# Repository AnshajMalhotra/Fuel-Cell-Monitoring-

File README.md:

# Project Seminar SS2025 — Fuel Cell Monitoring Board

A mixed-signal hardware and firmware project for monitoring fuel-cell voltage and current using a custom KiCad PCB, precision analog front-end, isolated SPI data path, 16-bit ADC acquisition, and ESP32-S3 based data processing.

This repository combines the complete PCB design files and embedded firmware developed for the **Project Seminar SS2025**. The board is intended to acquire fuel-cell electrical measurements, convert raw ADC data into physical voltage/current values, and stream the processed measurements to a host system over serial communication.

---

## Repository Description

**Short GitHub description:**

> KiCad + ESP32-S3 fuel-cell monitoring board with precision voltage/current sensing, 16-bit SPI ADC acquisition, digital isolation, and PlatformIO firmware for averaged serial data output.

---

## Project Overview

The project focuses on designing and implementing a fuel-cell monitoring board that can measure:

- Fuel-cell voltage
- Fuel-cell current
- ADC raw measurement values
- Averaged and calibrated output data

The system is built around a modular PCB design with separate schematic blocks for power, voltage measurement, current measurement, ADC conversion, data transmission, and microcontroller-side processing.

```mermaid
flowchart LR
    A[Fuel Cell Input] --> B[Voltage Measurement Stage]
    A --> C[Current Measurement Stage]
    B --> D[16-bit ADC]
    C --> D
    D --> E[Digital Isolation / SPI Interface]
    E --> F[ESP32-S3 Firmware]
    F --> G[Serial Output to Host]
```

---

## Key Features

- Custom PCB designed in **KiCad**
- Modular schematic structure for easier debugging and documentation
- Fuel-cell voltage sensing using a resistor divider and analog signal conditioning
- Fuel-cell current sensing using a shunt resistor and current-sense amplifier stage
- Precision voltage reference for ADC conversion
- SPI-based ADC communication
- Digital isolation for safer data transmission between analog and digital domains
- ESP32-S3 firmware using **PlatformIO** and the **Arduino framework**
- Timer-based sampling and averaging for stable readings
- Serial output in a simple host-readable format

---

## Hardware Architecture

| Block | Purpose | Related Files |
|---|---|---|
| Main KiCad Project | Central project configuration | `Project_Seminar_SS2025.kicad_pro` |
| PCB Layout | Physical board layout | `Project_Seminar_SS2025.kicad_pcb` |
| Root Schematic | Top-level schematic project | `Project_Seminar_SS2025.kicad_sch` |
| Power Supply | Power regulation and supply rails | `power.kicad_sch` |
| Voltage Measurement | Fuel-cell voltage sensing stage | `voltage_measure.kicad_sch`, `voltage_mea.kicad_sch` |
| Current Measurement | Shunt/current-sense stage | `current_measure.kicad_sch` |
| ADC Stage | ADC interface and analog conversion | `adc.kicad_sch`, `ADC_Main.kicad_sch` |
| Data Transmission | Isolated SPI / digital communication | `Data_Transmission_Main.kicad_sch` |
| Custom Symbols | Project-specific schematic symbols | `KiCad_Board_Design/MySymbols/` |
| Custom Footprints | Project-specific PCB footprints | `KiCad_Board_Design/MyFootprints/` |
| ERC Report | Electrical rules check output | `ERC.rpt` |

---

## Main Components Used

The design includes footprints/symbols for several important mixed-signal and embedded components, including:

- **ESP32-S3 DevKitC-1** — microcontroller and firmware execution platform
- **LTC2368IMS-16** — 16-bit ADC interface stage
- **LTC6655 4.096 V reference** — precision ADC reference
- **AD8410** — current-sense amplifier stage
- **LT6202** — analog signal conditioning / amplifier stage
- **ADuM4150BRIZ** — digital isolator for SPI communication
- **LT1761 / LT1762** — low-noise voltage regulators
- Custom connectors, jumpers, shunt resistor, and measurement terminals

---

## Firmware Overview

Firmware is located in:

```text
Board_Software/Fuel_Cell/
```

The ESP32-S3 firmware performs the following tasks:

1. Initializes serial communication at `115200 baud`
2. Configures SPI pins for ADC communication
3. Uses a hardware timer for periodic acquisition
4. Reads two 16-bit ADC channels from a 32-bit SPI transfer
5. Averages multiple samples for smoother measurements
6. Converts raw ADC values into voltage and current
7. Sends formatted readings to the host PC

### Firmware Pin Mapping

| Signal | ESP32-S3 Pin |
|---|---:|
| MOSI | GPIO 11 |
| MISO | GPIO 13 |
| SCK | GPIO 12 |
| SS / CS | GPIO 10 |
| CNV | GPIO 14 |
| BUSY | GPIO 9 |

### Serial Output Format

The firmware prints measurements in the following format:

```text
V:12.345,I:1.234
```

Where:

- `V` = calculated fuel-cell voltage in volts
- `I` = calculated fuel-cell current in amperes

---

## Measurement Conversion Logic

The firmware uses a 4.096 V ADC reference and 16-bit conversion range.

### Voltage Conversion

```cpp
adcInputVoltage = (rawValue / 65535.0) * 4.096;
fuelCellVoltage = adcInputVoltage * dividerRatio;
```

The voltage divider ratio is calculated from:

```cpp
R_TOTAL = 39000 + 2000;
R_BOTTOM = 3900 + 100;
dividerRatio = R_TOTAL / R_BOTTOM;
```

### Current Conversion

```cpp
senseAmpOutputVoltage = (rawValue / 65535.0) * 4.096;
shuntVoltage = senseAmpOutputVoltage / 20.0;
fuelCellCurrent = shuntVoltage / 0.008;
```

The current calculation depends on:

- Sense amplifier gain: `20`
- Shunt resistance used in firmware: `0.008 Ω`

> Update these constants if the final measured resistor values or amplifier gain differ from the prototype assumptions.

---

## Getting Started

### 1. Clone the Repository

```bash
git clone https://github.com/<your-username>/<your-repo-name>.git
cd <your-repo-name>
```

### 2. Open the PCB Design

Open the project file in KiCad:

```text
Project_Seminar_SS2025.kicad_pro
```

Recommended KiCad workflow:

1. Open the project in KiCad
2. Review the schematic hierarchy
3. Run ERC from the schematic editor
4. Open the PCB layout
5. Run DRC before manufacturing
6. Generate Gerber/drill files if the board is ready for fabrication

---

## Building and Uploading Firmware

### Prerequisites

Install:

- Visual Studio Code
- PlatformIO extension
- ESP32-S3 board support through PlatformIO
- USB driver for the ESP32-S3 board, if required

### Build Firmware

```bash
cd Board_Software/Fuel_Cell
pio run
```

### Upload Firmware

```bash
pio run --target upload
```

### Open Serial Monitor

```bash
pio device monitor -b 115200
```

Expected output:

```text
Fuel Cell Monitoring Board - Initializing...
Initialization Complete. Starting Data Acquisition.
V:12.345,I:1.234
```

---

## Repository Structure

```text
Project_Seminar_SS2025/
├── Project_Seminar_SS2025.kicad_pro       # Main KiCad project
├── Project_Seminar_SS2025.kicad_sch       # Top-level schematic
├── Project_Seminar_SS2025.kicad_pcb       # PCB layout
├── power.kicad_sch                        # Power supply design
├── current_measure.kicad_sch              # Current measurement circuit
├── voltage_measure.kicad_sch              # Voltage reference / measurement circuit
├── adc.kicad_sch                          # ADC schematic block
├── Data_Transmission_Main.kicad_sch       # Data transmission / isolation block
├── KiCad_Board_Design/
│   ├── MySymbols/                         # Custom KiCad symbols
│   └── MyFootprints/                      # Custom KiCad footprints
└── Board_Software/
    └── Fuel_Cell/
        ├── platformio.ini                 # PlatformIO configuration
        └── src/
            └── main.cpp                   # ESP32-S3 firmware
```

---

## Suggested GitHub Topics

Use these topics on GitHub to make the project easier to discover:

```text
kicad
pcb-design
esp32-s3
platformio
embedded-systems
fuel-cell
adc
spi
current-sensing
voltage-measurement
mixed-signal
arduino-framework
```

---

## Recommended Cleanup Before Publishing

Before pushing to GitHub, avoid committing generated or temporary files such as:

```text
.pio/
build/
*.bin
*.elf
*.map
*.o
*.d
*.bak
*.lck
Project_Seminar_SS2025-backups/
```

A cleaner repository will be smaller, easier to clone, and more professional for reviewers.

---

## Future Improvements

- Add calibration procedure for voltage and current measurements
- Add CSV logging or USB serial data parser on the host side
- Add OLED/display support for live local readings
- Add wireless transmission using Wi-Fi or BLE
- Add automated firmware tests for conversion functions
- Add final board render, schematic screenshots, and measurement results
- Generate Gerber files and attach manufacturing notes

---

## Author

**Anshaj Malhotra**  
M.Eng. Electrical and Information Engineering  
Hochschule Wismar

---

## License

No license has been selected yet. If this project is intended to be open-source, add a license such as MIT, Apache-2.0, or CERN-OHL depending on how you want others to use the hardware and software design.

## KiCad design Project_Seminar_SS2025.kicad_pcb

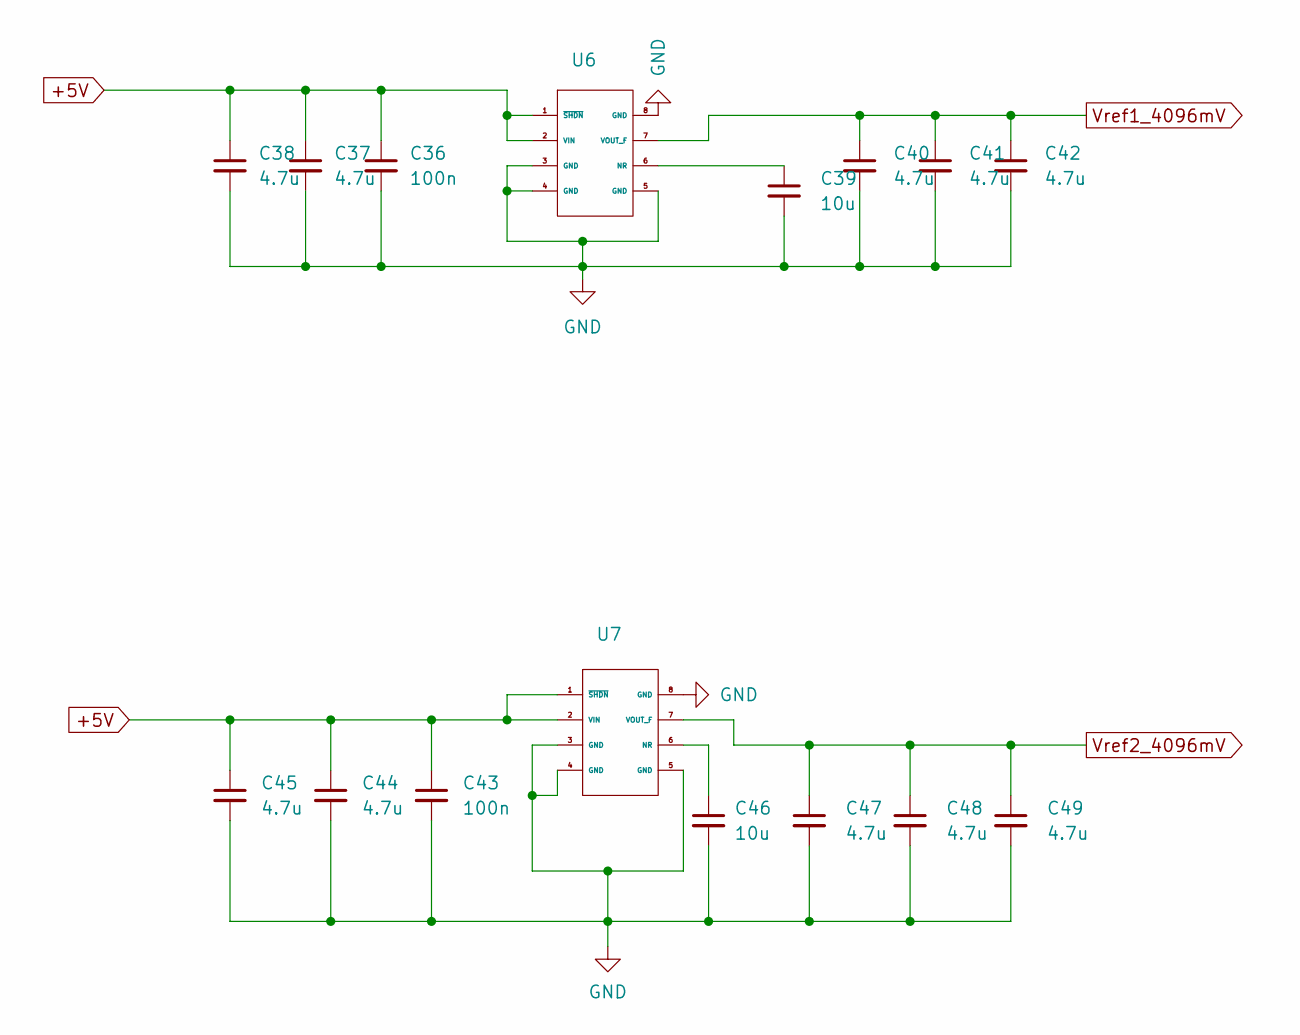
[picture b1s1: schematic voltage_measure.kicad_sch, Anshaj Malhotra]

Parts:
C36, C43: 100n; C_0201_0603Metric
C37, C38, C40, C41, C42, C44, C45, C47, C48, C49: 4.7u; C_0201_0603Metric
C39, C46: 10u; C_0201_0603Metric
U6, U7: LTC6655LNCHMS8-4.096#PBF

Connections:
+5V: C36.1, C37.1, C38.1, C43.1, C44.1, C45.1, U6.1 (~SHDN), U6.2 (VIN), U7.1 (~SHDN), U7.2 (VIN); also elsewhere on the board
GND: C36.2, C37.2, C38.2, C39.2, C40.2, C41.2, C42.2, C43.2, C44.2, C45.2, C46.2, C47.2, C48.2, C49.2, U6.3 (GND), U6.4 (GND), U6.5 (GND), U6.8 (GND), U7.3 (GND), U7.4 (GND), U7.5 (GND), U7.8 (GND); also elsewhere on the board
unnamed: C39.1, U6.6 (NR)
unnamed: C46.1, U7.6 (NR)
Vref1_4096mV: C40.1, C41.1, C42.1, U6.7 (VOUT_F); also elsewhere on the board
Vref2_4096mV: C47.1, C48.1, C49.1, U7.7 (VOUT_F); also elsewhere on the board

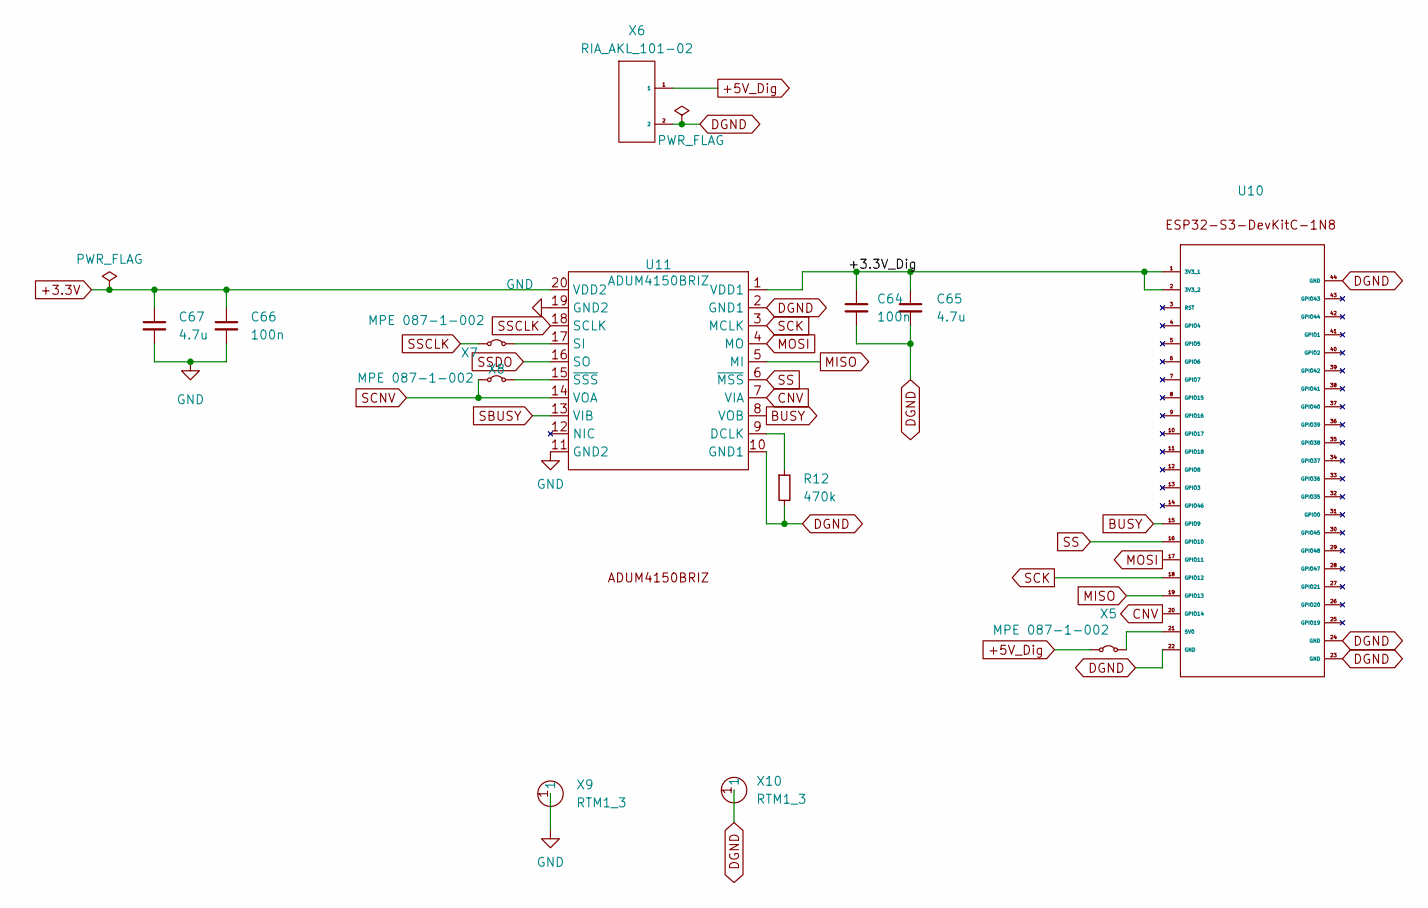
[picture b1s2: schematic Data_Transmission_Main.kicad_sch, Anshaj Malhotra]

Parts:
C64, C66: 100n; C_0201_0603Metric
C65, C67: 4.7u; C_0201_0603Metric
R12: 470k; R_0402_1005Metric
U10: ESP32
U11: ADUM4150BRIZ
X5, X7, X8: MPE 087-1-002; SolderJumper-2_P1.3mm_Bridged2Bar_Pad1.0x1.5mm
X6: RIA_AKL_101-02; AKL073-2
X9, X10: RTM1_3

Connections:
+3.3V: C66.1, C67.1, U11.20 (VDD2); also elsewhere on the board
+5V_Dig: X5.1 (A), X6.1
/Data transmission/+3.3V_Dig: C64.1, C65.1, U10.1 (3V3_1), U10.2 (3V3_2), U11.1 (VDD1)
BUSY: U10.15 (GPIO9), U11.8 (VOB)
CNV: U10.20 (GPIO14), U11.7 (VIA)
DGND: C64.2, C65.2, R12.2, U10.22 (GND), U10.23 (GND), U10.24 (GND), U10.44 (GND), U11.2 (GND1), U11.10 (GND1), X6.2, X10.1
GND: C66.2, C67.2, U11.11 (GND2), U11.19 (GND2), X9.1; also elsewhere on the board
MISO: U10.19 (GPIO13), U11.5 (MI)
MOSI: U10.17 (GPIO11), U11.4 (MO)
unnamed: U10.21 (5V0), X5.2 (B)
unnamed: R12.1, U11.9 (DCLK)
unnamed: U11.17 (SI), X7.2 (B)
unnamed: U11.15 (~SSS), X8.2 (B)
SBUSY: U11.13 (VIB); also elsewhere on the board
SCK: U10.18 (GPIO12), U11.3 (MCLK)
SCNV: U11.14 (VOA), X8.1 (A)
SS: U10.16 (GPIO10), U11.6 (~MSS)
SSCLK: U11.18 (SCLK), X7.1 (A)
SSDO: U11.16 (SO); also elsewhere on the board

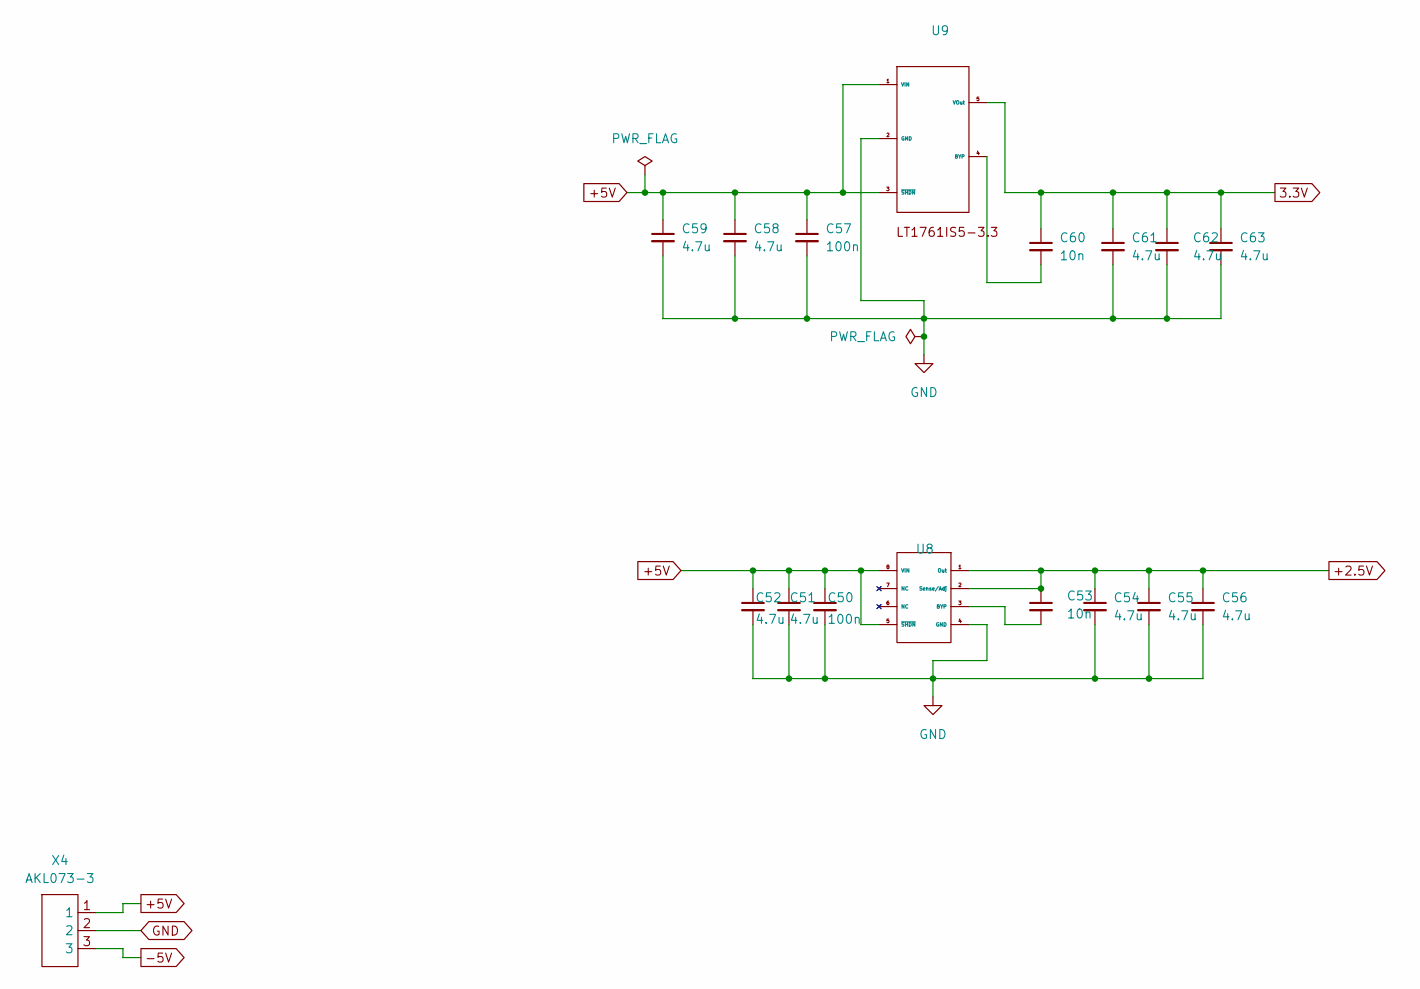
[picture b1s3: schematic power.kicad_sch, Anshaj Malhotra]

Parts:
C50, C57: 100n; C_0201_0603Metric
C51, C52, C54, C55, C56, C58, C59, C61, C62, C63: 4.7u; C_0201_0603Metric
C53, C60: 10n; C_0402_1005Metric
U8: LT1762EMS8-2v5
U9: LT1761IS5-3.3TRMPBF
X4: AKL073-3; Connector (AKL073-3)

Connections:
3.3V: C60.1, C61.1, C62.1, C63.1, U9.5 (VOut)
+2.5V: C53.1, C54.1, C55.1, C56.1, U8.1 (Out), U8.2 (Sense/Adj); also elsewhere on the board
+5V: C50.1, C51.1, C52.1, C57.1, C58.1, C59.1, U8.5 (~SHDN), U8.8 (VIN), U9.1 (VIN), U9.3 (~SHDN), X4.1; also elsewhere on the board
-5V: X4.3; also elsewhere on the board
GND: C50.2, C51.2, C52.2, C54.2, C55.2, C56.2, C57.2, C58.2, C59.2, C61.2, C62.2, C63.2, U8.4 (GND), U9.2 (GND), X4.2; also elsewhere on the board
unnamed: C53.2, U8.3 (BYP)
unnamed: C60.2, U9.4 (BYP)

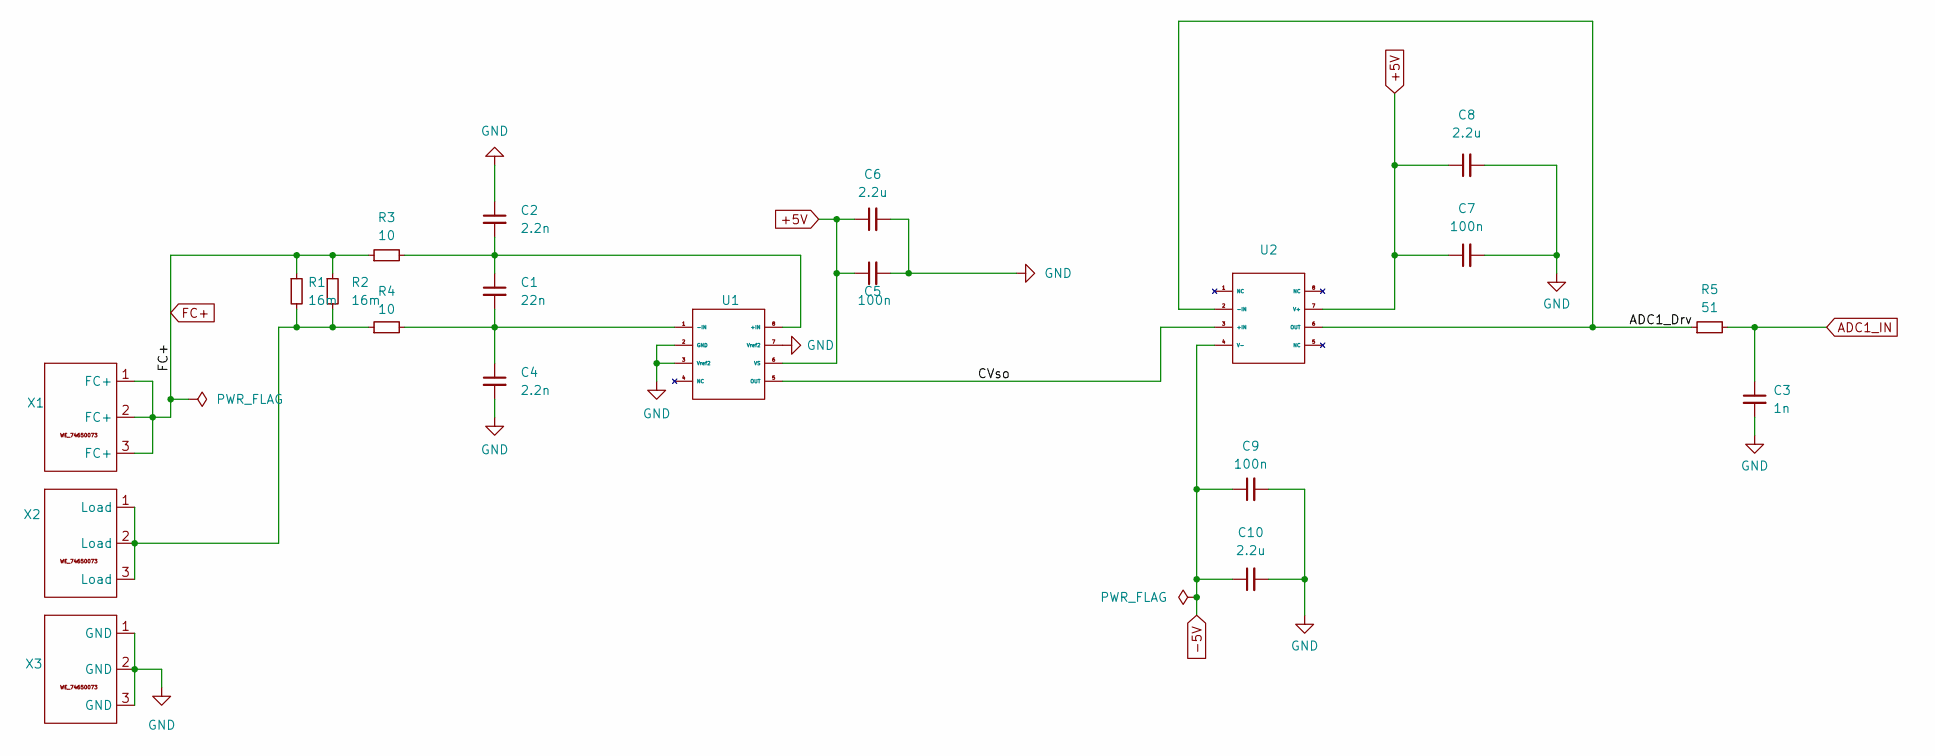
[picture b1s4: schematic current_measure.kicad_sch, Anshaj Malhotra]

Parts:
C1: 22n; C_0201_0603Metric
C2, C4: 2.2n; C_0201_0603Metric
C3: 1n; C_0201_0603Metric
C5, C7, C9: 100n; C_0201_0603Metric
C6, C8, C10: 2.2u; C_0201_0603Metric
R1, R2: 16m; R_2512_6332Metric
R3, R4: 10; R_0603_1608Metric
R5: 51; R_0603_1608Metric
U1: AD8410ABWRZ
U2: LT6202IS8
X1, X2, X3: WE_74650073

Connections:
+5V: C5.1, C6.1, C7.1, C8.1, U1.6 (VS), U2.7 (V+); also elsewhere on the board
-5V: C9.1, C10.1, U2.4 (V-); also elsewhere on the board
/current_measure/ADC1_Drv: R5.1, U2.2 (-IN), U2.6 (OUT)
/current_measure/CVso: U1.5 (OUT), U2.3 (+IN)
ADC1_IN: C3.1, R5.2; also elsewhere on the board
FC+: R1.1, R2.1, R3.1, X1.1 (FC+), X1.2 (FC+), X1.3 (FC+); also elsewhere on the board
GND: C2.1, C3.2, C4.2, C5.2, C6.2, C7.2, C8.2, C9.2, C10.2, U1.2 (GND), U1.3 (Vref2), U1.7 (Vref2), X3.1 (GND), X3.2 (GND), X3.3 (GND); also elsewhere on the board
unnamed: R1.2, R2.2, R4.1, X2.1 (Load), X2.2 (Load), X2.3 (Load)
unnamed: C1.1, C2.2, R3.2, U1.8 (+IN)
unnamed: C1.2, C4.1, R4.2, U1.1 (-IN)

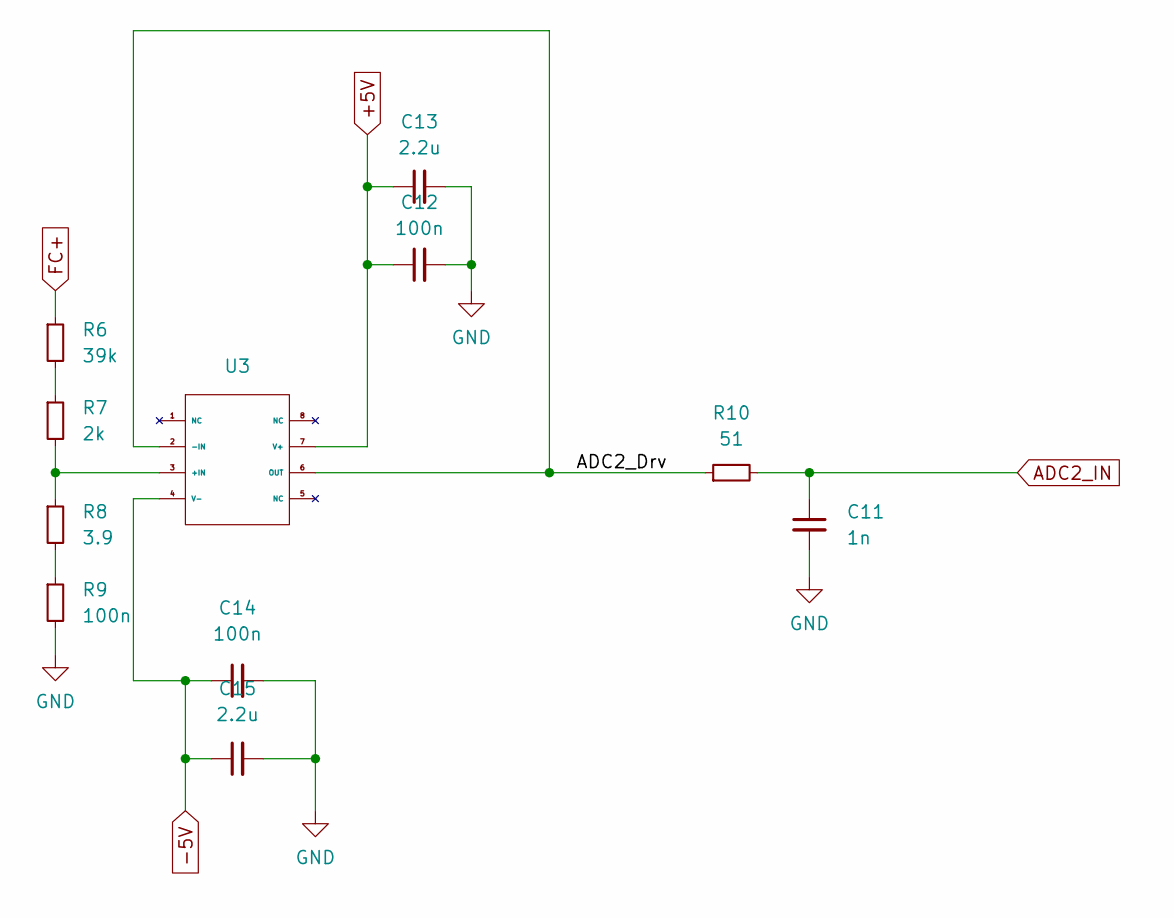
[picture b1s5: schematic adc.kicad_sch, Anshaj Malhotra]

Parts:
C11: 1n; C_0201_0603Metric
C12, C14: 100n; C_0201_0603Metric
C13, C15: 2.2u; C_0201_0603Metric
R6: 39k; R_0603_1608Metric
R7: 2k; R_0603_1608Metric
R8: 3.9; R_0603_1608Metric
R9: 100n; R_0603_1608Metric
R10: 51; R_0603_1608Metric
U3: LT6202IS8

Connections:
+5V: C12.1, C13.1, U3.7 (V+); also elsewhere on the board
-5V: C14.1, C15.1, U3.4 (V-); also elsewhere on the board
/voltage_measurement/ADC2_Drv: R10.1, U3.2 (-IN), U3.6 (OUT)
ADC2_IN: C11.1, R10.2; also elsewhere on the board
FC+: R6.1; also elsewhere on the board
GND: C11.2, C12.2, C13.2, C14.2, C15.2, R9.2; also elsewhere on the board
unnamed: R6.2, R7.1
unnamed: R8.2, R9.1
unnamed: R7.2, R8.1, U3.3 (+IN)

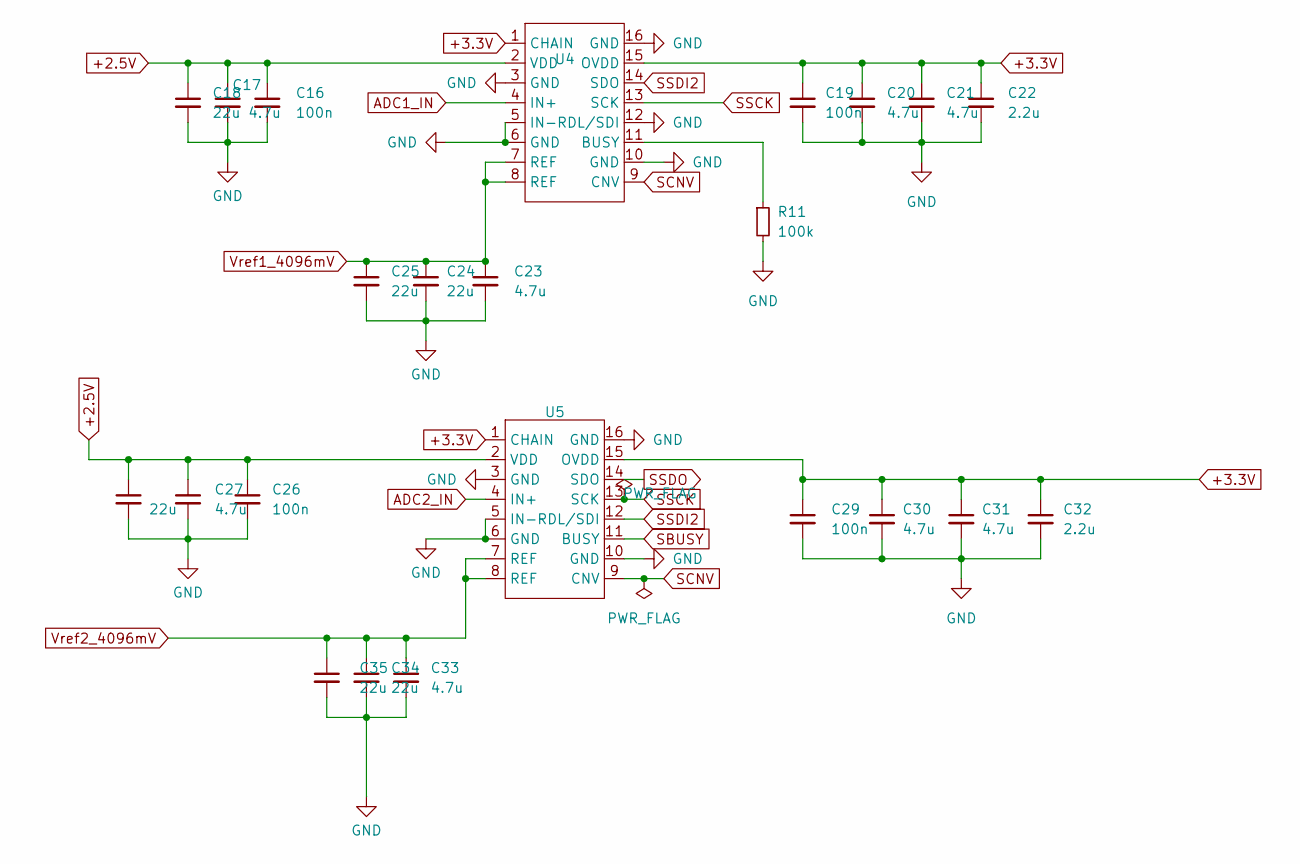
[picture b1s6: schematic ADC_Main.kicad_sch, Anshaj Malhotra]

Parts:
C16, C19, C26, C29: 100n; C_0201_0603Metric
C17, C20, C21, C23, C27, C30, C31, C33: 4.7u; C_0201_0603Metric
C18: 22u; C_0201_0603Metric
C22, C32: 2.2u; C_0201_0603Metric
C24, C25, C28, C34, C35: 22u; C_0805_2012Metric
R11: 100k; R_0603_1608Metric
U4, U5: LTC2368IMS-16

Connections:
+2.5V: C16.1, C17.1, C18.1, C26.1, C27.1, C28.1, U4.2 (VDD), U5.2 (VDD); also elsewhere on the board
+3.3V: C19.1, C20.1, C21.1, C22.1, C29.1, C30.1, C31.1, C32.1, U4.1 (CHAIN), U4.15 (OVDD), U5.1 (CHAIN), U5.15 (OVDD); also elsewhere on the board
ADC1_IN: U4.4 (IN+); also elsewhere on the board
ADC2_IN: U5.4 (IN+); also elsewhere on the board
GND: C16.2, C17.2, C18.2, C19.2, C20.2, C21.2, C22.2, C23.2, C24.2, C25.2, C26.2, C27.2, C28.2, C29.2, C30.2, C31.2, C32.2, C33.2, C34.2, C35.2, R11.2, U4.3 (GND), U4.5 (IN-), U4.6 (GND), U4.10 (GND), U4.12 (RDL/SDI), U4.16 (GND), U5.3 (GND), U5.5 (IN-), U5.6 (GND), U5.10 (GND), U5.16 (GND); also elsewhere on the board
unnamed: R11.1, U4.11 (BUSY)
SBUSY: U5.11 (BUSY); also elsewhere on the board
SCNV: U4.9 (CNV), U5.9 (CNV)
SSCK: U4.13 (SCK), U5.13 (SCK)
SSDI2: U4.14 (SDO), U5.12 (RDL/SDI)
SSDO: U5.14 (SDO); also elsewhere on the board
Vref1_4096mV: C23.1, C24.1, C25.1, U4.7 (REF), U4.8 (REF); also elsewhere on the board
Vref2_4096mV: C33.1, C34.1, C35.1, U5.7 (REF), U5.8 (REF); also elsewhere on the board

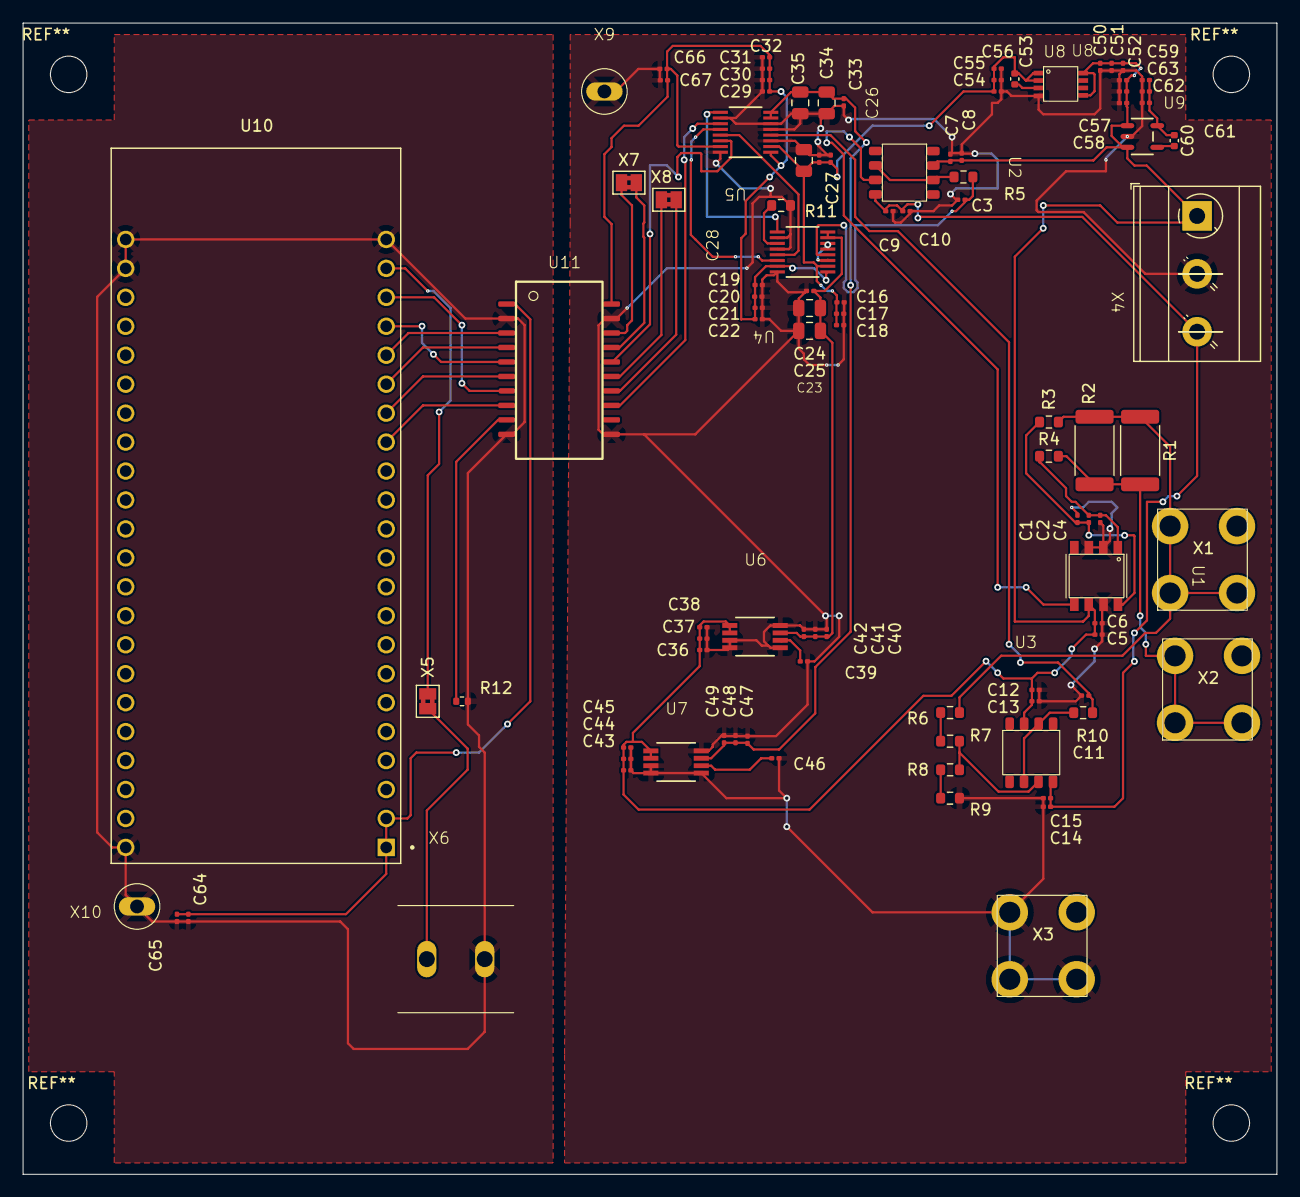
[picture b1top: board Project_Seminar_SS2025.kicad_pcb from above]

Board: 2 copper layers, 110.0 x 101.0 mm, 100 parts (0 on the bottom side), 45 nets.
